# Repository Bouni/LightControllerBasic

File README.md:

# LightControllerBasic

Basic version of my LightController

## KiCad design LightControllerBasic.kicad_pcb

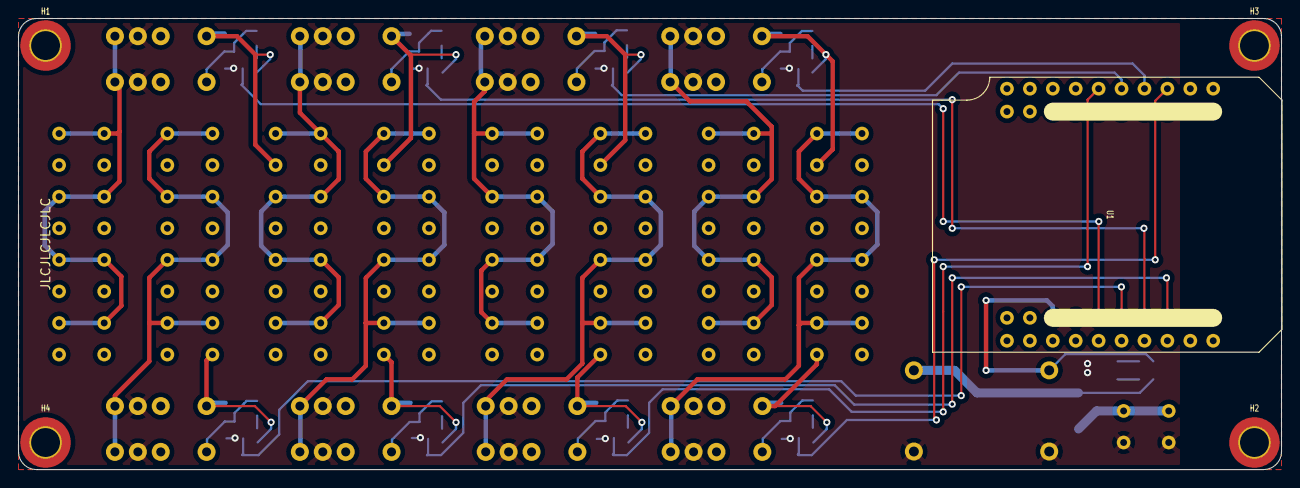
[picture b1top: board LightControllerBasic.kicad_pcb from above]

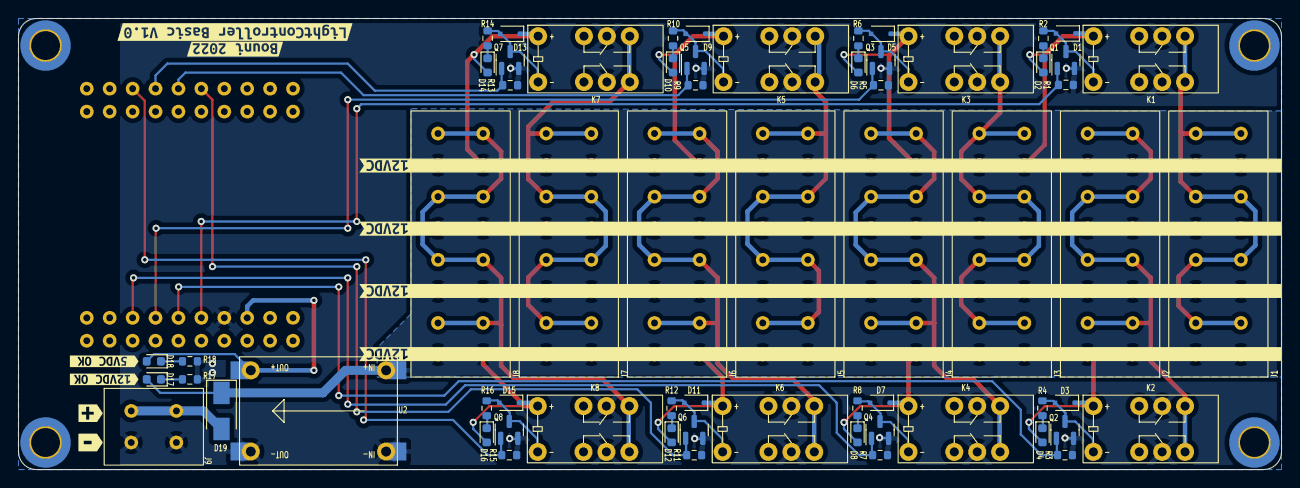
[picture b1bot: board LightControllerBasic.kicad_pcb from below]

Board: 2 copper layers, 140.0 x 50.0 mm, 78 parts (73 on the bottom side), 38 nets.

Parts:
D1, D3, D5, D7, D9, D11, D13, D15: 1N4148WS; D_SOD-323F
D2, D4, D6, D8, D10, D12, D14, D16, D17, D18: LED; LED_0603_1608Metric
D19: D_Schottky; D_SMA
H1, H2, H3, H4: MountingHole; MountingHole_3.2mm_M3_DIN965_Pad_TopBottom
J1, J2, J3, J4, J5, J6, J7, J8: Conn_01x08_Female; SPTAF_1_8_3_5_EL
J9: Conn_01x02_Female; SPTAF_1_2_3_5_EL
K1, K2, K3, K4, K5, K6, K7, K8: HONGFA-HFD3
Q1, Q2, Q3, Q4, Q5, Q6, Q7, Q8: AO3400A; SOT-23
R1, R3, R5, R7, R9, R11, R13, R15: 10k; R_0603_1608Metric
R2, R4, R6, R8, R10, R12, R14, R16, R17: 2k2; R_0603_1608Metric
R18: 680; R_0603_1608Metric
U1: mh-et-live-minikit; MH-ET LIVE MiniKit
U2: DCDC-Module
kibuzzard-62501B9E, kibuzzard-62501B9E#2, kibuzzard-62501B9E#3, kibuzzard-62501B9E#4: G***; kibuzzard-62501B9E
kibuzzard-62501C98: G***; kibuzzard-62501C98
kibuzzard-62501CB0: G***; kibuzzard-62501CB0
kibuzzard-6255152E: G***; kibuzzard-6255152E
kibuzzard-62551477: G***; kibuzzard-62551477
kibuzzard-62551484: G***; kibuzzard-62551484
kibuzzard-62551550: G***; kibuzzard-62551550

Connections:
+5V: D18.2 (A), U1.28 (5V), U2.3 (OUT+)
+12V: D1.1 (K), D2.2 (A), D3.1 (K), D4.2 (A), D5.1 (K), D6.2 (A), D7.1 (K), D8.2 (A), D9.1 (K), D10.2 (A), D11.1 (K), D12.2 (A), D13.1 (K), D14.2 (A), D15.1 (K), D16.2 (A), D17.2 (A), D19.1 (K), J1.1, J1.3, J1.5, J1.7, J2.1, J2.3, J2.5, J2.7, J3.1, J3.3, J3.5, J3.7, J4.1, J4.3, J4.5, J4.7, J5.1, J5.3, J5.5, J5.7, J6.1, J6.3, J6.5, J6.7, J7.1, J7.3, J7.5, J7.7, J8.1, J8.3, J8.5, J8.7, K1.1, K2.1, K3.1, K4.1, K5.1, K6.1, K7.1, K8.1, U2.2 (IN+)
GND: J9.2, K1.4, K1.9, K2.4, K2.9, K3.4, K3.9, K4.4, K4.9, K5.4, K5.9, K6.4, K6.9, K7.4, K7.9, K8.4, K8.9, Q1.2 (S), Q2.2 (S), Q3.2 (S), Q4.2 (S), Q5.2 (S), Q6.2 (S), Q7.2 (S), Q8.2 (S), R1.1, R3.1, R5.1, R7.1, R9.1, R11.1, R13.1, R15.1, R17.2, R18.2, U1.27 (GND), U2.1 (IN-), U2.4 (OUT-)
unnamed: D1.2 (A), K1.12, Q1.3 (D), R2.2
unnamed: D2.1 (K), R2.1
unnamed: D3.2 (A), K2.12, Q2.3 (D), R4.2
unnamed: D4.1 (K), R4.1
unnamed: D5.2 (A), K3.12, Q3.3 (D), R6.2
unnamed: D6.1 (K), R6.1
unnamed: D7.2 (A), K4.12, Q4.3 (D), R8.2
unnamed: D8.1 (K), R8.1
unnamed: D9.2 (A), K5.12, Q5.3 (D), R10.2
unnamed: D10.1 (K), R10.1
unnamed: D11.2 (A), K6.12, Q6.3 (D), R12.2
unnamed: D12.1 (K), R12.1
unnamed: D13.2 (A), K7.12, Q7.3 (D), R14.2
unnamed: D14.1 (K), R14.1
unnamed: D15.2 (A), K8.12, Q8.3 (D), R16.2
unnamed: D16.1 (K), R16.1
unnamed: D17.1 (K), R17.1
unnamed: D18.1 (K), R18.1
unnamed: D19.2 (A), J9.1
unnamed: J1.2, J1.4, J1.6, J1.8, K1.5, K1.8
unnamed: J2.2, J2.4, J2.6, J2.8, K2.5, K2.8
unnamed: J3.2, J3.4, J3.6, J3.8, K3.5, K3.8
unnamed: J4.2, J4.4, J4.6, J4.8, K4.5, K4.8
unnamed: J5.2, J5.4, J5.6, J5.8, K5.5, K5.8
unnamed: J6.2, J6.4, J6.6, J6.8, K6.5, K6.8
unnamed: J7.2, J7.4, J7.6, J7.8, K7.5, K7.8
unnamed: J8.2, J8.4, J8.6, J8.8, K8.5, K8.8
OUT0: Q1.1 (G), R1.2, U1.26 (IO16)
OUT1: Q2.1 (G), R3.2, U1.25 (IO17)
OUT2: Q3.1 (G), R5.2, U1.24 (IO21)
OUT3: Q4.1 (G), R7.2, U1.23 (IO22)
OUT4: Q5.1 (G), R9.2, U1.5 (IO33)
OUT5: Q6.1 (G), R11.2, U1.6 (IO34)
OUT6: Q7.1 (G), R13.2, U1.4 (IO35)
OUT7: Q8.1 (G), R15.2, U1.3 (SVN)

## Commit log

2022-04-08 add screenshots
2022-04-13 minor adjustments
2022-05-02 add ESPhome firmware definition
2022-06-21 add secrets
